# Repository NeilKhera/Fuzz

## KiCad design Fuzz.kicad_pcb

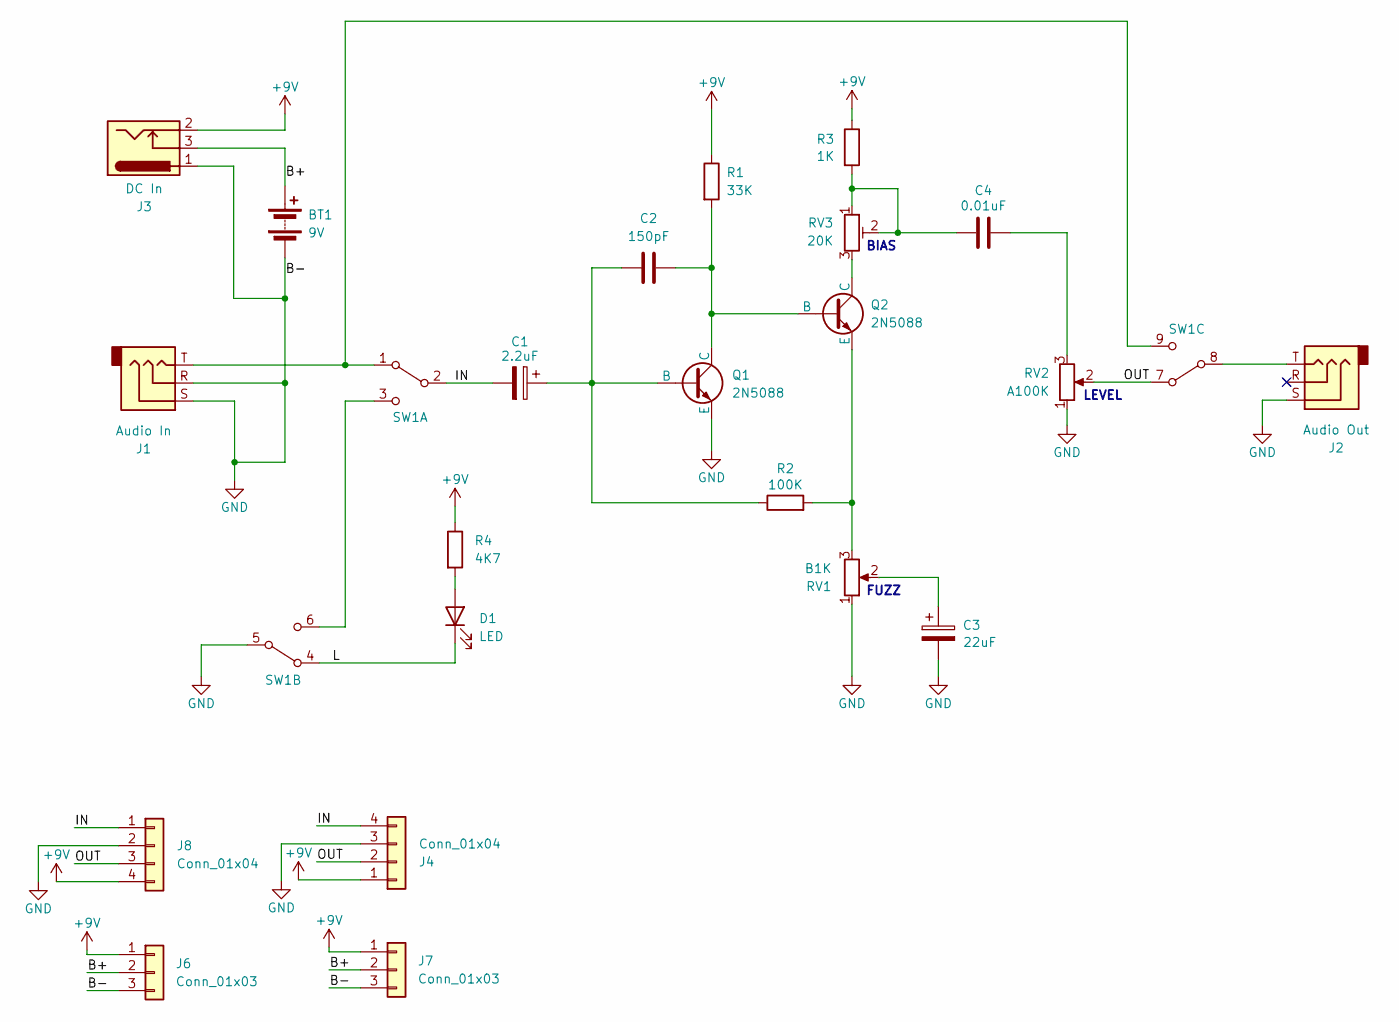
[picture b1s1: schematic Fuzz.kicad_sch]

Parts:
BT1: 9V; PinHeader_1x02_P2.54mm_Vertical
C1: 2.2uF; CP_Radial_D8.0mm_P3.50mm
C2: 150pF; C_Rect_L7.0mm_W4.5mm_P5.00mm
C3: 22uF; CP_Radial_D8.0mm_P3.50mm
C4: 0.01uF; C_Rect_L7.2mm_W2.5mm_P5.00mm_FKS2_FKP2_MKS2_MKP2
D1: LED; LED_D5.0mm
J1: Audio In; Jack_6.35mm_Neutrik_NMJ6HCD2_Horizontal
J2: Audio Out; Jack_6.35mm_Neutrik_NMJ6HCD2_Horizontal
J3: DC In; BarrelJack_Horizontal
J4: Conn_01x04; PinSocket_1x04_P2.54mm_Vertical
J6, J7: Conn_01x03; PinHeader_1x03_P2.54mm_Vertical
J8: Conn_01x04; PinHeader_1x04_P2.54mm_Vertical
Q1, Q2: 2N5088; TO-92_Inline
R1: 33K; R_Axial_DIN0204_L3.6mm_D1.6mm_P7.62mm_Horizontal
R2: 100K; R_Axial_DIN0204_L3.6mm_D1.6mm_P7.62mm_Horizontal
R3: 1K; R_Axial_DIN0204_L3.6mm_D1.6mm_P7.62mm_Horizontal
R4: 4K7; R_Axial_DIN0204_L3.6mm_D1.6mm_P7.62mm_Horizontal
RV1: B1K; Potentiometer_Alpha_RD901F-40-00D_Single_Vertical
RV2: A100K; Potentiometer_Alpha_RD901F-40-00D_Single_Vertical
RV3: 20K; Potentiometer_Alpha_RD901F-40-00D_Single_Vertical
SW1: SW_TPDT_x3; 3PDT

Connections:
+9V: J3.2, J4.1, J6.1, J7.1, J8.4, R1.1, R3.1, R4.1
/B+: BT1.1 (+), J3.3, J6.2, J7.2
/IN: C1.2, J4.4, J8.1, SW1.2 (B)
/L: D1.1 (K), SW1.4 (A)
/OUT: J4.2, J8.3, RV2.2, SW1.7 (A)
GND: BT1.2 (-), C3.2, J1.R, J1.S, J2.S, J3.1, J4.3, J6.3, J7.3, J8.2, Q1.3 (E), RV1.1, RV2.1, SW1.5 (B)
unnamed: C3.1, RV1.2
unnamed: C4.1, R3.2, RV3.1, RV3.2
unnamed: C4.2, RV2.3
unnamed: D1.2 (A), R4.2
unnamed: C1.1, C2.1, Q1.2 (B), R2.1
unnamed: C2.2, Q1.1 (C), Q2.2 (B), R1.2
unnamed: Q2.1 (C), RV3.3
unnamed: Q2.3 (E), R2.2, RV1.3
unnamed: J1.T, SW1.1 (A), SW1.9 (C)
unnamed: SW1.3 (C), SW1.6 (C)
unnamed: J2.T, SW1.8 (B)

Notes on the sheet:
BIAS
LEVEL
FUZZ

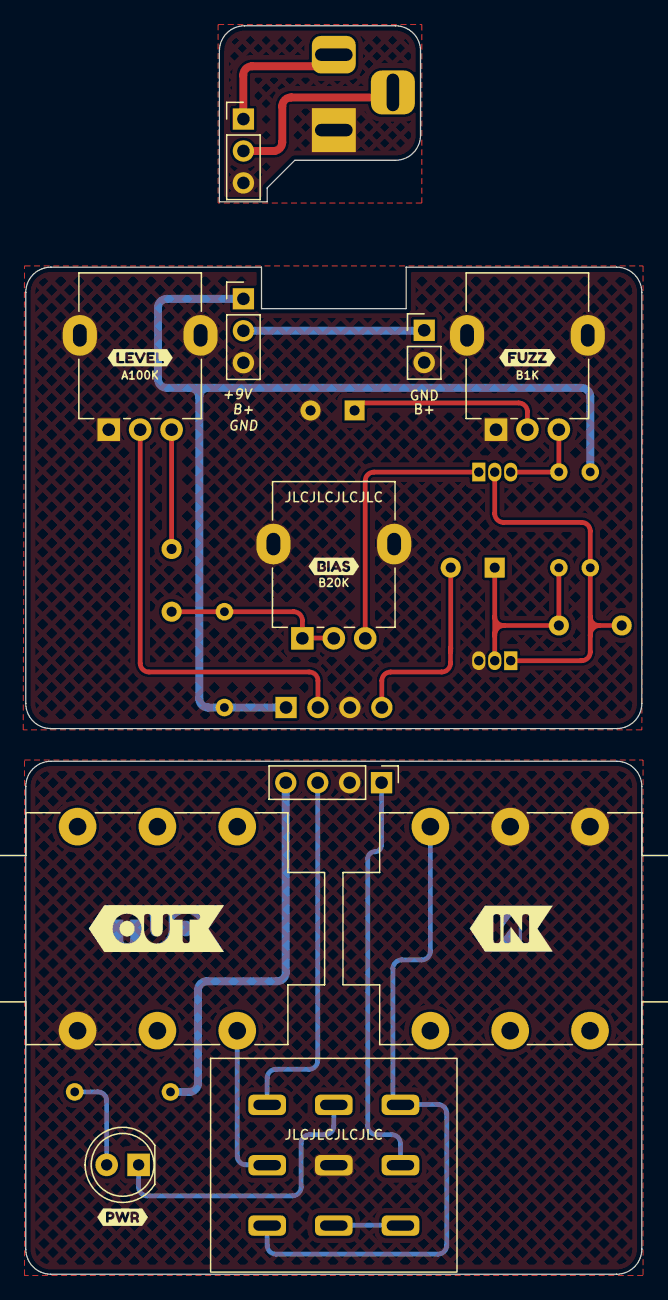
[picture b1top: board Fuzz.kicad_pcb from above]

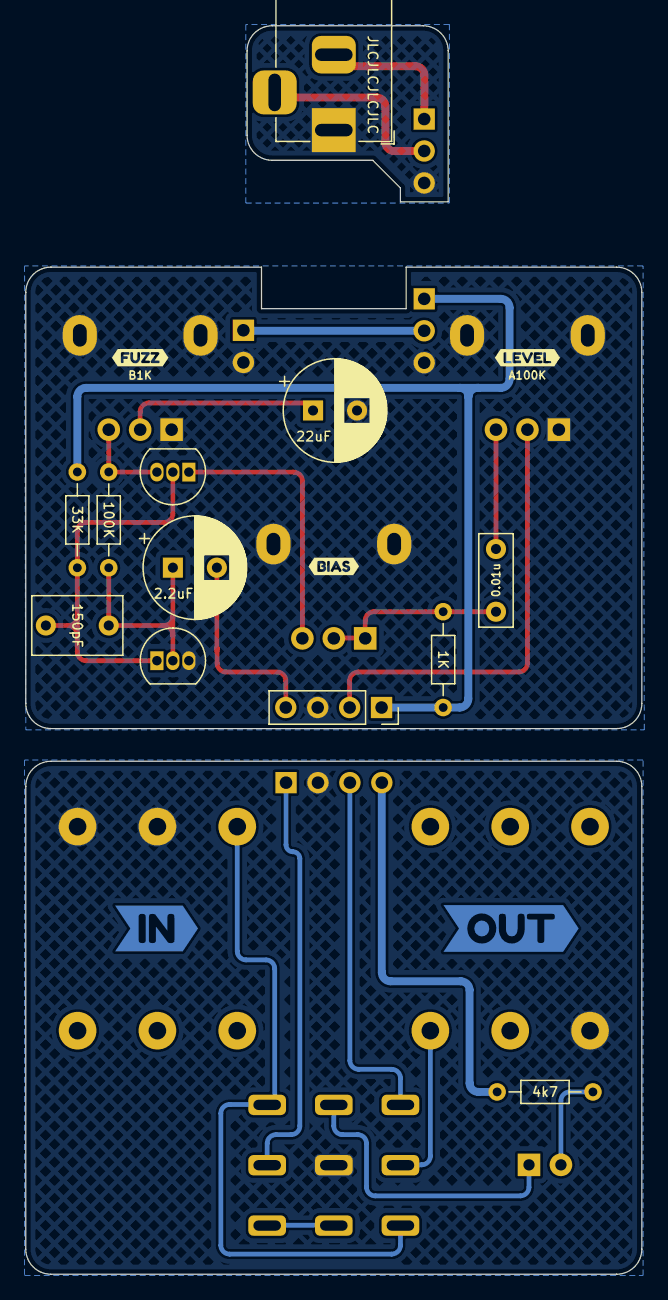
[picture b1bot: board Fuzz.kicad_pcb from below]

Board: 2 copper layers, 49.0 x 99.3 mm, 34 parts (17 on the bottom side), 17 nets.

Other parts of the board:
kibuzzard-6566ADCD, kibuzzard-6566ADCD#2: G***; kibuzzard-6566ADCD
kibuzzard-6566AFB7: G***; kibuzzard-6566AFB7
kibuzzard-6566B0F9: G***; kibuzzard-6566B0F9
kibuzzard-6566B11B: G***; kibuzzard-6566B11B
kibuzzard-6566B130: G***; kibuzzard-6566B130
kibuzzard-6566B525: G***; kibuzzard-6566B525
kibuzzard-6566B576, kibuzzard-6566B576#2: G***; kibuzzard-6566B576
kibuzzard-65663E0B, kibuzzard-65663E0B#2: G***; kibuzzard-65663E0B

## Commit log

2024-05-03 Added .gitignore
2024-05-03 File upload
